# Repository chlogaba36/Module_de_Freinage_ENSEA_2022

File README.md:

# Module_de_Freinage_ENSEA_2022

<h5>
Dans le cadre de projet de 1ère année à l'ENSEA, nous avons créé un frein pour moteur à courant continue reposant sur le principe de résitance dissipative.
Notre module est alimenté par la source de la MCC et permet via une interface homme-machine de sélectionner les tensions de seuil ainsi que d'avoir un mode manuel.
Sur ce github se trouve les datasheets des éléments utilisés, les éléments de la partie hardware, IHM ainsi que le projet sous STM32CubeIDE.
  
Actuellement, la library de l'écran LCD est complète et fonctionnelle avec une documentation Doxygen, le codeur incrémental et le driver n'ont pas encore été mis en place et le fonctionnement global n'a pas pu être testé.

Pour plus d'information, voir le cahier des charges(disponible dans le dossier livrable)
</h5>

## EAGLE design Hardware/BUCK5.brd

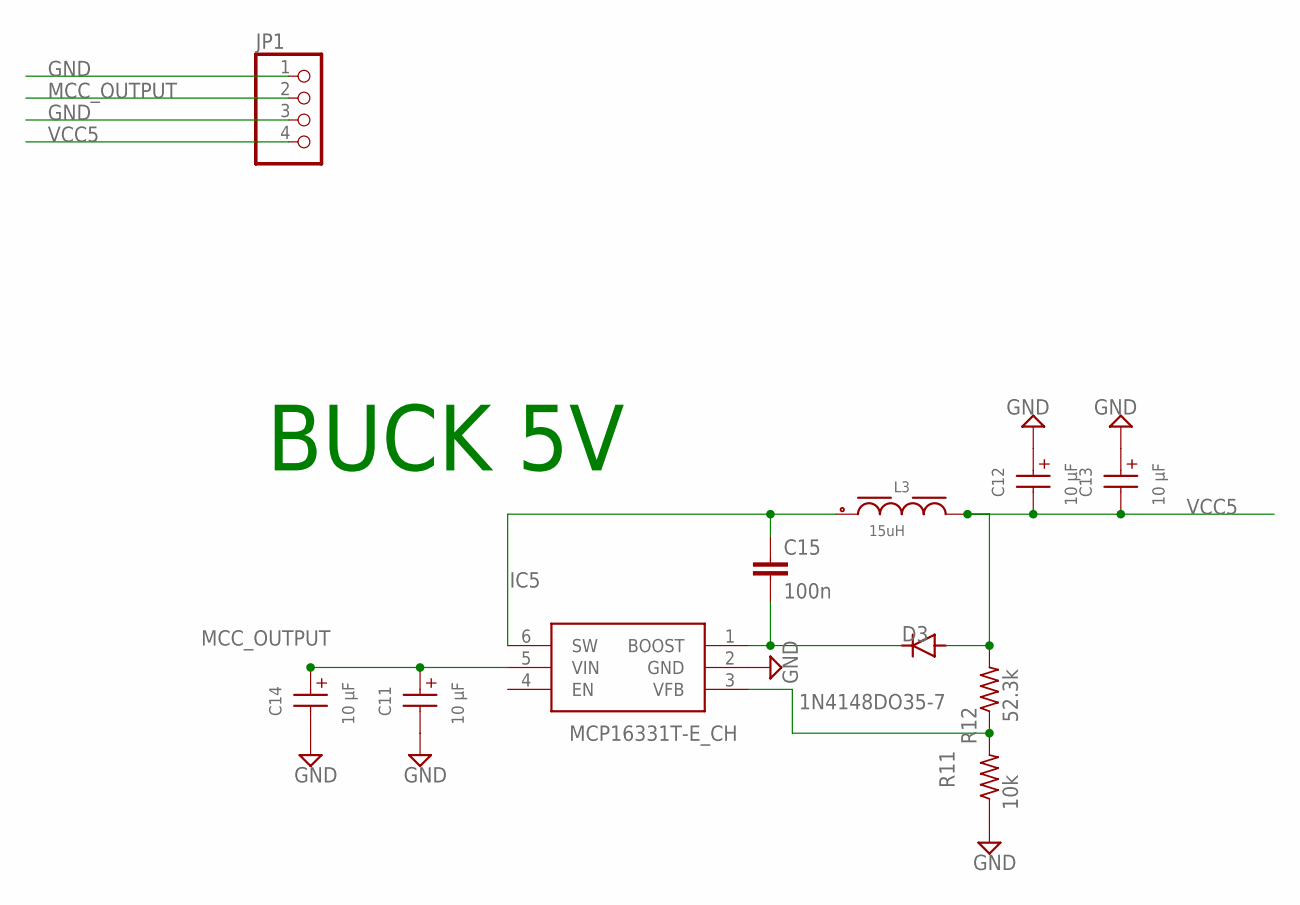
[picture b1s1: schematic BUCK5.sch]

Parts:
C11, C12, C13, C14: 10 µF; WCAP-ASLI_6.3X7.7(DXL)
C15: 100n; C0805
D3: 1N4148DO35-7; DO35-7
IC5: MCP16331T-E_CH; SOT95P280X145-6N
JP1: PINHD-1X4; 1X04
L3: 15uH; WE-PD_7345R
R11: 10k; R0603
R12: 52.3k; R0603

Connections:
GND: C11.2 (-), C12.1 (+), C13.1 (+), C14.2 (-), IC5.2 (GND), JP1.1, JP1.3, R11.1
MCC_OUTPUT: C11.1 (+), C14.1 (+), IC5.5 (VIN), JP1.2
unnamed: C15.1, IC5.6 (SW), L3.1
unnamed: C15.2, D3.C, IC5.1 (BOOST)
unnamed: IC5.3 (VFB), R11.2, R12.1
VCC5: C12.2 (-), C13.2 (-), D3.A, JP1.4, L3.2, R12.2

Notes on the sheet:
BUCK 5V

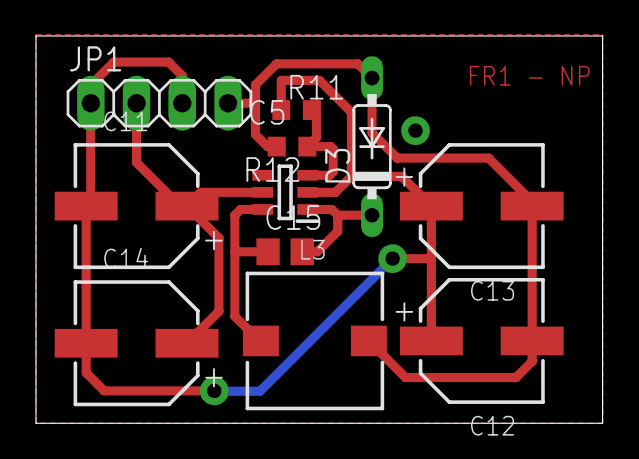
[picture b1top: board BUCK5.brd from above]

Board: 2 copper layers, 31.5 x 21.5 mm, 11 parts (0 on the bottom side), 6 nets.

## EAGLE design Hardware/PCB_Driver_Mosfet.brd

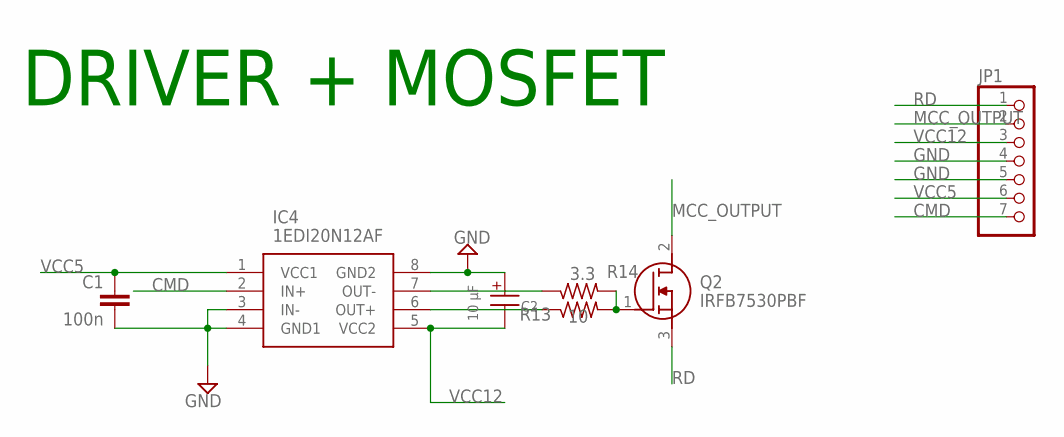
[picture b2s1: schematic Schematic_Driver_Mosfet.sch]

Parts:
C1: 100n; C0805
C2: 10 µF; WCAP-ASLI_6.3X7.7(DXL)
IC4: 1EDI20N12AF; SOIC127P600X175-8N
JP1: PINHD-1X7/90; 1X07/90
Q2: IRFB7530PBF; TO254P483X1016X1994-3P
R13: 10; R0603
R14: 3.3; R0603

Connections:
CMD: IC4.2 (IN+), JP1.7
GND: C2.1 (+), IC4.3 (IN-), IC4.8 (GND2), JP1.4, JP1.5
MCC_OUTPUT: JP1.2, Q2.2 (D)
unnamed: IC4.6 (OUT+), R13.1
unnamed: IC4.7 (OUT-), R14.1
unnamed: C1.2, IC4.4 (GND1)
unnamed: Q2.1 (G), R13.2, R14.2
RD: JP1.1, Q2.3 (S)
VCC12: C2.2 (-), IC4.5 (VCC2), JP1.3
VCC33: C1.1, IC4.1 (VCC1), JP1.6

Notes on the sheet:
DRIVER + MOSFET

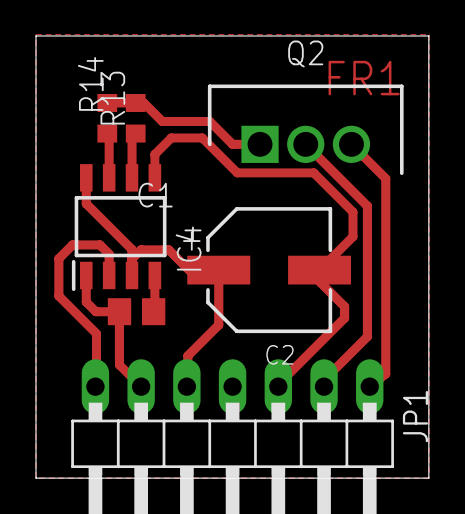
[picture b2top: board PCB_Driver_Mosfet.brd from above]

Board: 2 copper layers, 21.8 x 24.6 mm, 7 parts (0 on the bottom side), 10 nets.

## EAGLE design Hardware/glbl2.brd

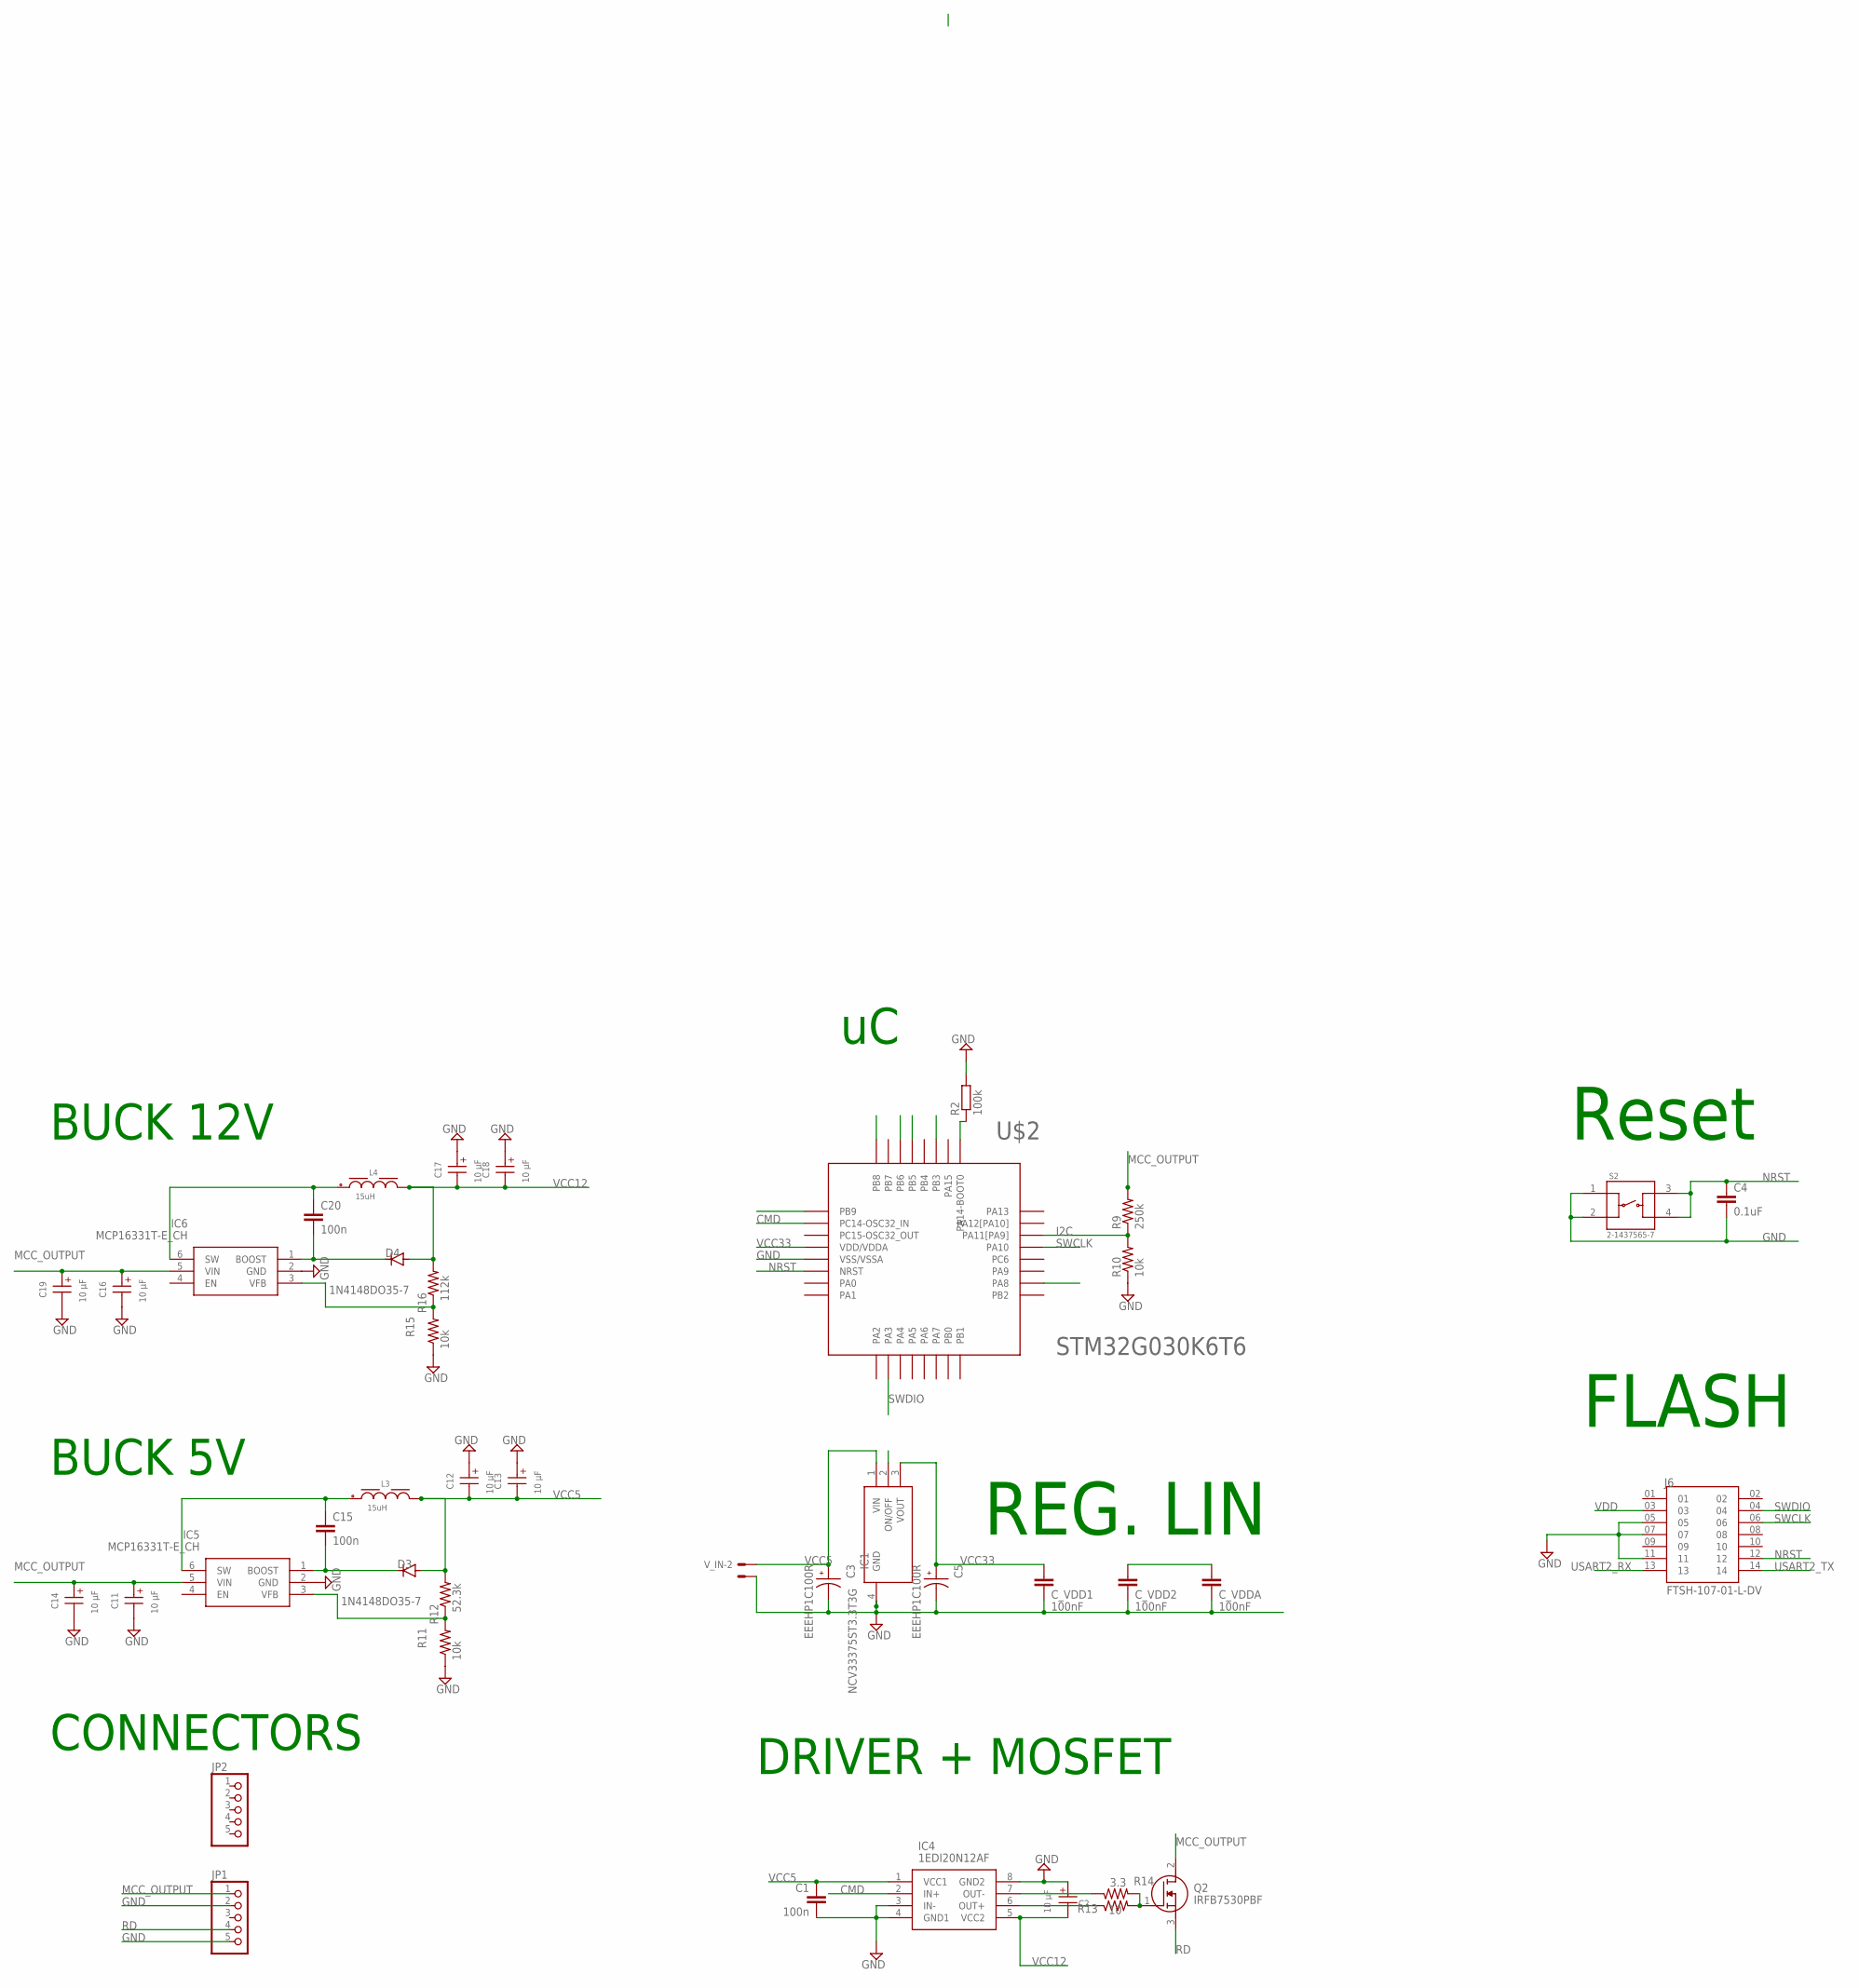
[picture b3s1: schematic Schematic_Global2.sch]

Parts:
C1, C15, C20: 100n; C0805
C2, C11, C12, C13, C14, C16, C17, C18, C19: 10 µF; WCAP-ASLI_6.3X7.7(DXL)
C3, C5: EEEHP1C100R; CAP_EEEHP1C100R
C4: 0.1uF; C0603
C_VDD1, C_VDD2: 100nF; C0603
C_VDDA: 100nF; C0603
D3, D4: 1N4148DO35-7; DO35-7
IC1: NCV33375ST3.3T3G; SOT230P700X175-4N
IC4: 1EDI20N12AF; SOIC127P600X175-8N
IC5, IC6: MCP16331T-E_CH; SOT95P280X145-6N
J6: FTSH-107-01-L-DV; SAMTEC_FTSH-107-01-L-DV
JP1, JP2: PINHD-1X5; 1X05
L3, L4: 15uH; WE-PD_7345R
Q2: IRFB7530PBF; TO254P483X1016X1994-3P
R2: 100k; R0603
R9: 250k; R0603
R10, R11, R15: 10k; R0603
R12: 52.3k; R0603
R13: 10; R0603
R14: 3.3; R0603
R16: 112k; R0603
S2: 2-1437565-7; SW_2-1437565-7
U$2: STM32G030K6T6; QFP32_STM32
V_IN: 22-23-2021

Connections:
CMD: IC4.2 (IN+), U$2.2 (PC14-OSC32_IN)
GND: C2.1 (+), C3.2, C4.2, C5.2, C11.2 (-), C12.1 (+), C13.1 (+), C14.2 (-), C16.2 (-), C17.1 (+), C18.1 (+), C19.2 (-), C_VDD1.2, C_VDD2.2, C_VDDA.2, IC1.4 (GND), IC4.3 (IN-), IC4.8 (GND2), IC5.2 (GND), IC6.2 (GND), J6.05, J6.07, J6.11, JP1.2, JP1.5, R2.2, R10.1, R11.1, R15.1, S2.1, S2.2, U$2.5 (VSS/VSSA), V_IN.1
I2C: R9.1, R10.2, U$2.22 (PA11[PA9])
MCC_OUTPUT: C11.1 (+), C14.1 (+), C16.1 (+), C19.1 (+), IC5.5 (VIN), IC6.5 (VIN), JP1.1, Q2.2 (D), R9.2
unnamed: IC4.6 (OUT+), R13.1
unnamed: IC4.7 (OUT-), R14.1
unnamed: C_VDD2.1, C_VDDA.1
unnamed: C1.2, IC4.4 (GND1)
unnamed: R2.1, U$2.25 (PA14-BOOT0)
unnamed: C15.1, IC5.6 (SW), L3.1
unnamed: Q2.1 (G), R13.2, R14.2
unnamed: C15.2, D3.C, IC5.1 (BOOST)
unnamed: IC5.3 (VFB), R11.2, R12.1
unnamed: C20.1, IC6.6 (SW), L4.1
unnamed: C20.2, D4.C, IC6.1 (BOOST)
unnamed: IC6.3 (VFB), R15.2, R16.1
NRST: C4.1, J6.12, S2.3, S2.4, U$2.6 (NRST)
RD: JP1.4, Q2.3 (S)
SWCLK: J6.06, U$2.21 (PA10)
SWDIO: J6.04, U$2.10 (PA3)
USART2_RX: J6.13
USART2_TX: J6.14
VCC5: C1.1, C3.1, C12.2 (-), C13.2 (-), D3.A, IC1.1 (VIN), IC4.1 (VCC1), L3.2, R12.2, V_IN.2
VCC12: C2.2 (-), C17.2 (-), C18.2 (-), D4.A, IC4.5 (VCC2), L4.2, R16.2
VCC33: C5.1, C_VDD1.1, IC1.3 (VOUT), U$2.4 (VDD/VDDA)
VDD: J6.03

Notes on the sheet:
BUCK 12V
BUCK 5V
CONNECTORS
DRIVER + MOSFET
Reset
REG. LIN
FLASH

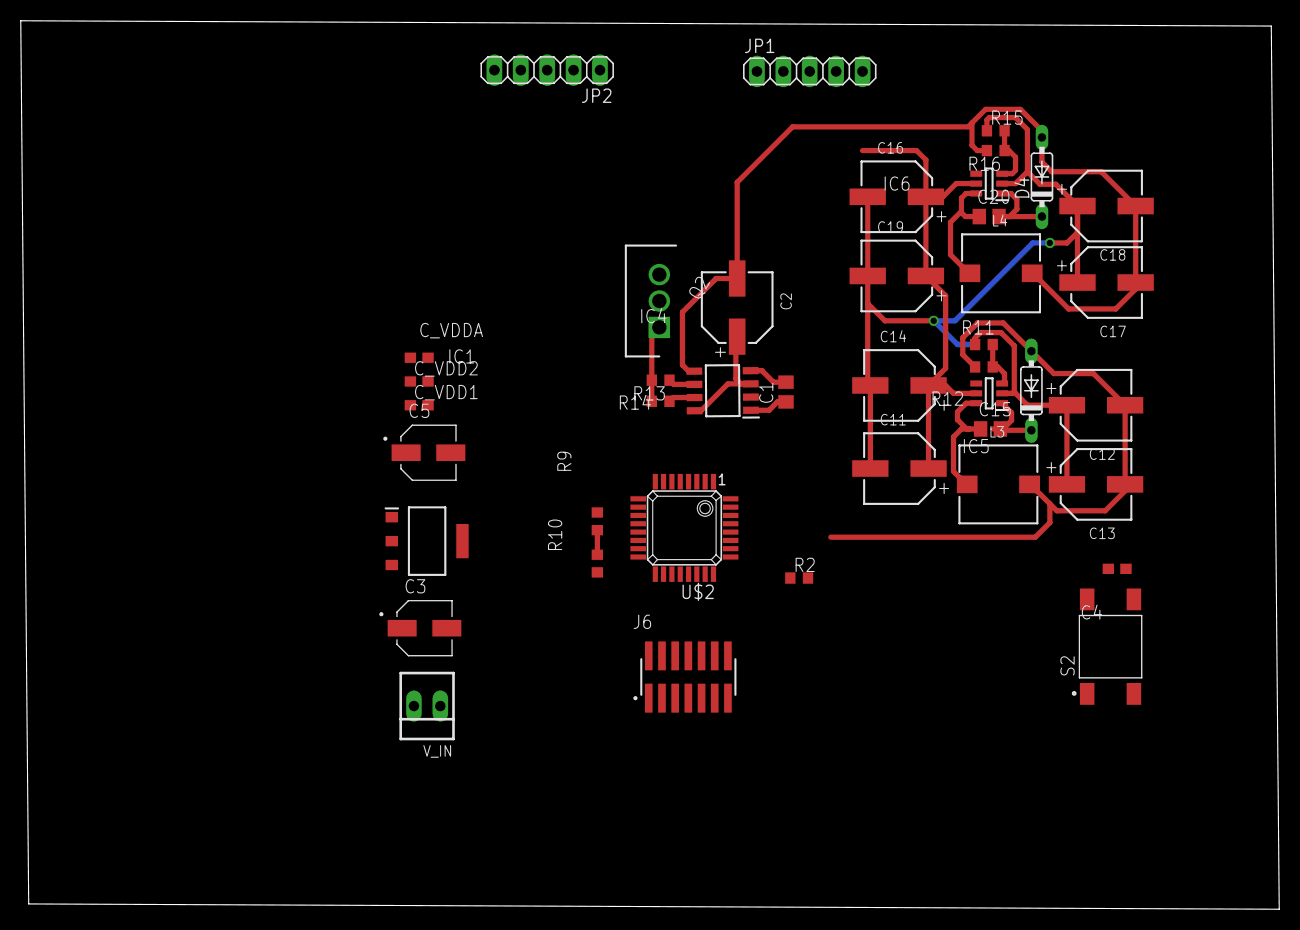
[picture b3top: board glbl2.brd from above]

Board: 2 copper layers, 121.1 x 85.5 mm, 42 parts (0 on the bottom side), 23 nets.

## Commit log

2022-05-31 Create Description
2022-06-01 Update Description
2022-06-01 Update Description_IHM
2022-06-01 Create Description_IHM
2022-06-01 Rename BUCK5.brd to PCB_BUCK5.brd
2022-06-01 Rename drivermos.brd to PCB_Driver_Mosfet.brd
2022-06-01 Rename drivermos.sch to Schematic_Driver_Mosfet.sch
2022-06-01 Rename BUCK5.sch to Schematic_BUCK5.sch
2022-06-01 Rename glbl2.brd to PCB_Global2.brd
2022-06-01 Rename glbl2.sch to Schematic_Global2.sch
2022-06-01 Rename Description_IHM to Description_IHM.md

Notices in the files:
parts and their libraries:
Eagle_WCAP-ASLI: Copyright: Würth Elektronik
